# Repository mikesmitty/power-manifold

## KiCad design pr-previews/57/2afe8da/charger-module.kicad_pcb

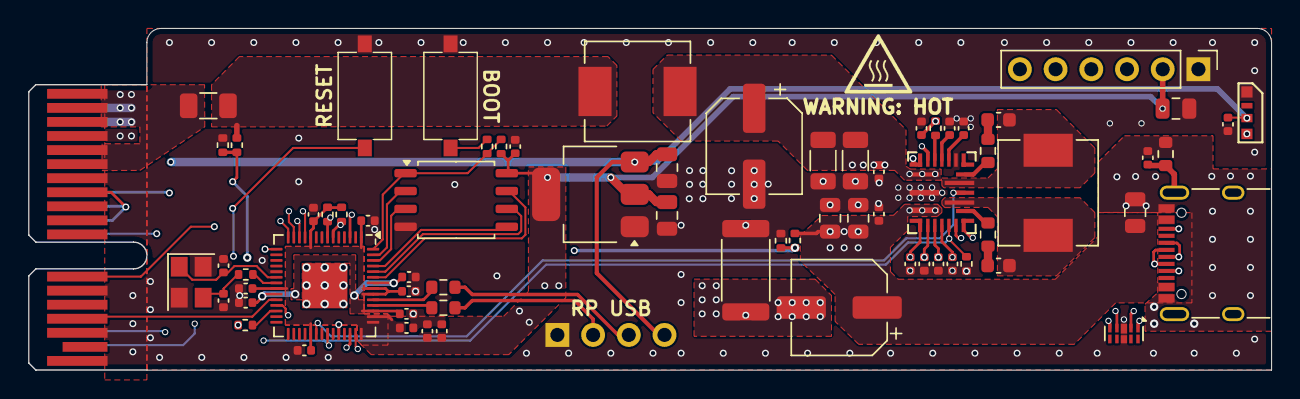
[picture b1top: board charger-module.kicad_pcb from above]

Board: 4 copper layers, 88.4 x 24.3 mm, 71 parts (1 on the bottom side), 54 nets.

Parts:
C1, C4, C21, C24, C28, C36: 10uF; C_0805_2012Metric
C2, C3: 39pF; C_0402_1005Metric
C5, C6, C9, C14, C15, C17, C20, C22, C25, C26, C27, C30, C35: 100nF; C_0402_1005Metric
C7, C10, C16, C37: 2.2uF; C_0402_1005Metric
C8, C31, C32, C33, C34: 470pF; C_0402_1005Metric
C11, C29: 100uF; CP_Elec_6.3x7.7
C12, C13: 4.7uF; C_1206_3216Metric
C18, C23: 220nF; C_0603_1608Metric
C19: 4.7nF; C_0402_1005Metric
D1: TPD4EUSB30; Diodes_UDFN-10_1.0x2.5mm_P0.5mm
D2: STATUS_LED; LED_Neopixel_Side_Light_SK6812
F1: 8A; Fuse_1206_3216Metric
J1: Conn_01x06_Pin; PinHeader_1x06_P2.54mm_Vertical
J2: Bus_PCI_Express_x1; BUS_PCIexpress_x1
J3: RP_USB; PinHeader_1x04_P2.54mm_Vertical
J4: USB_C_Receptacle_USB2.0_14P; USB_C_Receptacle_XKB_U262-16XN-4BVC11
L1, L2: 4.7uH; L_Sunlord_MWSA0603S
R1, R3, R4: 1K; R_0402_1005Metric
R2, R5, R11, R13: 10K; R_0402_1005Metric
R6: R010; R_2512_6332Metric
R7: 10R; R_0603_1608Metric
R8: 4.7K; R_0402_1005Metric
R9, R10: 27R; R_0603_1608Metric
R12: 0R; R_0603_1608Metric
R14, R16: 22K; R_0402_1005Metric
R15: 2K; R_0402_1005Metric
R17: 3.3K; R_0402_1005Metric
R18: 100K; R_0603_1608Metric
SW1: BOOT; XKB_TS-1101_SWITCH
SW2: RESET; XKB_TS-1101_SWITCH
U1: AMS1117-3.3; SOT-223-3_TabPin2
U2: W25Q32JVSSIQ; SOIC-8_5.23x5.23mm_P1.27mm
U3: RP2040; QFN-56-1EP_7x7mm_P0.4mm_EP3.2x3.2mm
U4: MPQ4242; MPQ4242_QNF-22_4mmx5mm
Y1: X322512MSB4SI; Crystal_SMD_3225-4Pin_3.2x2.5mm

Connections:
+1V1: C6.1, C9.1, C10.1, U3.23 (DVDD), U3.45 (VREG_VOUT), U3.50 (DVDD)
+3.3V: C4.1, C5.1, C15.1, C16.1, C17.1, C20.1, C22.1, C25.1, C27.1, C30.1, C36.1, J1.2, R2.1, R11.1, R13.1, U1.2 (VO), U2.8 (VCC), U3.1 (IOVDD), U3.10 (IOVDD), U3.22 (IOVDD), U3.33 (IOVDD), U3.42 (IOVDD), U3.43 (ADC_AVDD), U3.44 (VREG_IN), U3.48 (USB_VDD), U3.49 (IOVDD)
+5V: C1.1, C37.1, D2.2 (VDD), J2.A9 (+3.3V), J2.A10 (+3.3V), J2.B8 (+3.3V), J3.4, U1.3 (VI)
/EMI_VIN: C11.1, C12.1, C13.1, C14.1, L1.2, U4.1 (VIN)
/GPIO8: J1.3, U3.11 (GPIO8)
/GPIO9: J1.4, U3.12 (GPIO9)
/GPIO10: J1.5, U3.13 (GPIO10)
/GPIO11: J1.6, U3.14 (GPIO11)
/INDUCTOR: C18.2, L2.1, U4.14 (SW1)
/OUTDUCTOR: C23.1, L2.2, U4.12 (SW2)
/QSPI_SCLK: U2.6 (CLK), U3.52 (QSPI_SCLK)
/QSPI_SD0: U2.5 (DI(IO0)), U3.53 (QSPI_SD0)
/QSPI_SD1: U2.2 (DO(IO1)), U3.55 (QSPI_SD1)
/QSPI_SD2: U2.3 (IO2), U3.54 (QSPI_SD2)
/QSPI_SD3: U2.7 (IO3), U3.51 (QSPI_SD3)
/QSPI_SS: R1.1, R2.2, U2.1 (~CS), U3.56 (QSPI_SS)
/RUN: R4.2, U3.26 (RUN)
/SWCLK: J2.B15 (PETn0), U3.24 (SWCLK)
/SWD: J2.A11 (~PERST), U3.25 (SWD)
/VIN_PREFUSE: F1.2, J2.A1 (~PRSNT1), J2.A2 (+12V), J2.A3 (+12V), J2.B1 (+12V), J2.B2 (+12V), J2.B3 (+12V), J2.B5 (SMCLK), J2.B6 (SMDAT)
/XIN: C2.1, U3.20 (XIN), Y1.1
/XOUT: R3.1, U3.21 (XOUT)
ALERT: J2.A17 (PERn0), U3.15 (GPIO12)
CC1: C33.1, D1.5 (D2-), J4.A5 (CC1), U4.7 (CC1)
CC2: C34.1, D1.1 (D1+), J4.B5 (CC2), U4.4 (CC2)
D+: C32.1, D1.2 (D1-), J4.A6 (D+), J4.B6 (D+), U4.5 (DP)
D-: C31.1, D1.4 (D2+), J4.A7 (D-), J4.B7 (D-), U4.6 (DM)
ENABLE: U3.34 (GPIO22), U4.13 (EN)
GND: C1.2, C2.2, C3.2, C4.2, C5.2, C6.2, C7.2, C8.2, C9.2, C10.2, C11.2, C12.2, C13.2, C14.2, C15.2, C16.2, C17.2, C19.1, C20.2, C21.2, C22.2, C24.2, C25.2, C26.2, C27.2, C30.2, C31.2, C32.2, C33.2, C34.2, C36.2, C37.2, D1.3 (GND), D1.8 (GND), D2.4 (GND), J1.1, J2.A4 (GND), J2.A5 (JTAG2), J2.A6 (JTAG3), J2.A12 (GND), J2.A15 (GND), J2.A18 (GND), J2.B4 (GND), J2.B7 (GND), J2.B13 (GND), J2.B16 (GND), J2.B18 (GND), J3.1, R5.2, R6.1, R15.2, R17.2, SW1.1, SW2.1, U1.1 (GND), U2.4 (GND), U3.19 (TESTEN), U3.57 (GND), U4.2 (PGND), U4.17 (AGND), U4.21 (ISENS-), Y1.2, Y1.4
GNDUSB: C28.1, C29.2, C35.2, J4.A1 (GND), J4.A12 (GND), J4.B1 (GND), J4.B12 (GND), R6.2, R18.2, U4.22 (ISENS+)
IMON: C19.2, R8.1, U3.38 (GPIO26_ADC0)
LED_DIN: D2.1 (DIN), U3.3 (GPIO1)
unnamed: C3.1, R3.2, Y1.3
unnamed: C18.1, R7.2
unnamed: C23.2, R12.1
unnamed: C35.1, J4.S1 (SHIELD), R18.1
unnamed: R1.2, SW1.2
unnamed: R4.1, SW2.2
unnamed: R10.2, U3.46 (USB_DM)
unnamed: R9.2, U3.47 (USB_DP)
unnamed: R7.1, U4.15 (BST1)
unnamed: R12.2, U4.11 (BST2)
unnamed: R8.2, U4.20 (GPIO1)
unnamed: C8.1, U4.19 (ICOMP)
OVERLOAD: J2.A16 (PERp0), R5.1, U3.36 (GPIO24), U4.8 (GPIO2)
RP_D+: J3.3, R9.1
RP_D-: J3.2, R10.1
SCL: J2.B12 (RSVD), R13.2, U3.7 (GPIO5), U4.10 (SCL)
SDA: J2.A8 (JTAG5), R11.2, U3.6 (GPIO4), U4.9 (SDA)
VBUS: C21.1, C24.1, C26.1, C28.2, C29.1, J4.A4 (VBUS), J4.A9 (VBUS), J4.B4 (VBUS), J4.B9 (VBUS), R16.1, U4.3 (OUT)
VCC: C7.1, U4.18 (VCC)
VIN: F1.1, L1.1, R14.1
VIN_DIVIDER: R14.2, R15.1, U3.40 (GPIO28_ADC2)
VOUT_DIVIDER: R16.2, R17.1, U3.41 (GPIO29_ADC3)
